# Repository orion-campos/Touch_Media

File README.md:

# INFO
- Thesis Project Title: Touch Media
- MASTER IN ADVANCED ARCHITECTURE
- Institute of Advanced Architecture of Catalonia IAAC
- Research Line: Advanced Interaction 2015
- Author: Orion Gorrão Moreira Campos
- GitHub: [https://github.com/orion-campos/Touch_Media](https://github.com/orion-campos/Touch_Media)
- Thesis book: [https://issuu.com/home/published/orion_booklet](https://issuu.com/home/published/orion_booklet)
- Video 1: [Touch Media - Electronic Development](https://vimeo.com/manage/videos/140458246)
- Video 2: [Touch Media - 3D Printing Development](https://vimeo.com/manage/videos/140481266)

# GENERAL INFORMATION
This project is the result of six months of theoretical research and three months of complete dedication at the research line Advanced Interaction, as part of the Master of Advanced Architecture program at the Institute of Advanced Architecture of Catalonia. Because of this, it is possible to develop it more with proper time and resources.<br>
The author is sharing it under under the Apache License Version 2.0, so like other free software licenses, it allows the user of the software the freedom to use for any purpose, to distribute it, to modify it, and to distribute modified versions of the software. It still requires application of the same license to all unmodified parts and, in every licensed file, any original copyright, patent, trademark, and attribution notices in redistributed code must be preserved and, in every licensed file changed, a notification must be added stating that changes have been made to that file. The README file should be ALWAYS MAINTAINED IN ALL COPIES.<br>
Feel free to contact me if necessary :blush:<br>
<br>

# GITHUB FILES
**3D:**<br>
All the 3D printed geometries for the electronic compartments of the first user (the wrist) and the second user (the back pack and the DC motors vibrators). There is the original Rhino file of all, if it is desired to modify anything, and the STL of each part for being 3D printed.<br>
**ARDUINO:**<br>
All the Arduino codes, photos of the circuits, and the Fritzing files of each of the main steps of the development of the project, including the final one. They are organized numerically from 1 to FINAL.<br>
**CONCEPT:**<br>
Illustrations showing the initial concept of the objects that were aimed to create. The illustrations are conceptual, so they form just represent a desirable initial feeling.<br>
**EAGLE_PCBmilling:**<br>
Eagle files of the PCB’s made for the Arduino shields of the Arduino Micro (First user - emitter) and the Arduino UNO (Second user - receiver). Together with all the Eagle files, also the bitmap masks of each board, with the engrave and cut information for the Fabmodules to run.<br>
**PHOTOS:**<br>
Photos of the final prototype of the Glove part and the Back-pack part.<br>
**NOTICE:**<br>
The current Markdown file, that must be included as a readable copy within a README file distributed as part of the derivative works, within the source form or documentation, or within a display generated by the derivative works, as stipulated under the Apache License Version 2.0.<br>

# OBJECTIVE
This research aims to create a new way of communication using and increasing our sense of touch by creating a wearable tool, which has an open use, but in this research will focus to give a critical answer to our major visual based society. The main areas where this new form of communication can be used are:
- Helping vision disabled people, which then could have another option to communicate other than the braille language;
- Connecting users in a long distant relationship, which want to experience another type of connection that the visual devices cannot create; and
- People who want to experience and receive other types of information that couldn‘t been send by visual communication devices.

# PRODUCED OBJECT
A glove wearied by the first user, with 3 flex-sensors and 2 pressure sensors. This glove would be connected to a box attached to the wrist of the first user, containing all the electronic parts necessary to code the information from those sensors and send, via a radio frequency emitter, the information to the second user.<br>
The second user would be wearing a little back-pack with all the electronic parts necessary to code the information received via a radio frequency receiver, and transform it into movement of 6 DC Motors attached to its back, that would turn and rotate a weight on each motor, making the whole enclosure vibrate. The intensity and the length of the vibration of each motor would be determined by the intensity and the length of each sensor being pressed or bended.

# ELECTRONIC AND CODING TOOLS AND METHODS USED
The whole prototype of the electronic and coding part of the project was done with the open-source computer hardware and software Arduino.<br>
Arduino is based on a family of micro-controller board manufactured primarily by SmartProjects in Italy, using various 8-bit Atmel AVR micro-controllers or 32-bit Atmel ARM processors. These systems provide sets of digital and analog I/O pins that can be interfaced to various expansion boards and other circuits. The boards feature serial communications interfaces, including USB on some models, for loading programs from personal computers. For programming the micro-controllers, the Arduino platform provides an integrated development environment (IDE) based on the Processing project, which includes support for C and C++ programming languages.<br>
After the electronic prototype part it was used the software Fritzing, which is an open source software initiative to support designers and artists. It was developed at the University of Applied Sciences of Potsdam. The main advantage of the software is the easy interface to document and record the layout of the created breadboards.<br>

# ELECTRONIC COMPONENTS LIST
### First user - emitter
GLOVE PART
- 1x Arduino Micro;
- 1x RF Link Transmitter - 315MHz (https://www.sparkfun.com/products/10535);
- 3x Long Flex sensor-Length: 112.5mm (https://www.adafruit.com/products/182);
- 2x Round Force-Sensitive Resistor (FSR) - Interlink 402-Length:: 56.77mm (https://www.adafruit.com/products/166);
- 6x 22Kohm Resistor;
- 1x 10Kohm Resistor;
- 1x 220ohm Resistor;
- 1x LED;
- 1x Simple Switch;
- 1x 7.4V 400mAh Lipo battery; and
- 30CMx Hard copper wire to serve as antenna.

### Second user - receiver
BACK PACK PART
- 1x Arduino UNO R2 (UNO R3 should work as well);
- 1x RF Link Receiver - 4800bps (315MHz) (https://www.sparkfun.com/products/10533);
- 6x 1N4004 Diode;
- 6x TIP120 Transistor;
- 6x 10Kohm Resistor;
- 1x Simple Switch;
- 1x 7.4V 400mAh Lipo battery;
- 4x AA battery;
- 2x Double AA battery holder;
- 1x 7.4V 400mAh Lipo battery; and
- 30centimeterx Hard copper wire to serve as antenna.

VIBRATORS PART
- 6x 1.5-4.5V DC Motor (130 size).

### NECESSARY ELECTRONIC SUPPLIES
- 1x Lipo battery charger;
- 1x USB cable - A/MicroB;
- 1x USB Cable - Standard A-B;
- 1x Cooper plate for PCB milling;
- 5meterx Soft core electronic wire (aprox.28AWG); and
- 1x Soldering iron.

### OPTIONAL ELECTRONIC SUPPLIES
- 2meterx 6mm Heat Shrink.

# CIRCUIT BOARD PROJECT AND METHOD OF FABRICATION
After all the electronic components were tested and improved at the Protoboard, it was necessary to make a final shield for the Arduino in order to decrease the size of the circuit, make it user friendly, and more important, make it portable!<br>
It was used the software CAD Soft EAGLE for creating the schematic and the board design. EAGLE (for: Easily Applicable Graphical Layout Editor, German: Einfach anzuwendender grafischer Layout-Editor) by CadSoft Computer is a flexible, expandable and scriptable EDA application with schematic capture editor, PCB layout editor, auto-router and CAM and BOM tools developed by CadSoft Computer GmbH, Germany, since 1988. EAGLE is popular among smaller design houses and in academia for its favorable licensing terms and rich availability of component libraries on the web. Hobbyists are attracted by the availability of freeware licenses.<br>
After the board was designed with the most efficient use of the small space available, the CNC code was generated. Due to try and error process, a more fast speed configuration was used, making only five offset paths of cut in each line. The software used for this was the Fabmodules.<br>
- Video 1: [Touch Media - Electronic Development](https://vimeo.com/manage/videos/140458246)

# HARDWARE METHOD OF FABRICATION
For fabricating the cases of the DC Motors, the Arduino‘s and the produced Shields, it was created a series of compartments using a 3D Printer. This option was chosen due to the geometry that would be created, and the possibility to change and improve the final result easily.<br>
The method of 3D Printing used was an additive one, using PLA filaments. The 3d Printer was the BCN3D+, an open hardware based on the mechanic of the RapRap Prussa, developed by the Universidad Politecnica de Catalunya and assembled by the author.<br>
The file for the machine to print is know as G-Code. This file is a series of numbers that represent the position of the Nozller and the speed that the extruder need to go to the current point from the previous point. The G-Code was generated using the Slic3r software, a free software that generate the G-Code file, by configurations defined by the user, such as height of each layer, temperature, percentage of the fill of each solid, style of the fill, etc. The Slic3r software need as a basic input the base geometry to be 3d printed. This geometry was made using the Rhino software, but could be generated by any major 3D modeler.<br>
- Video 2: [Touch Media - 3D Printing Development](https://vimeo.com/manage/videos/140481266)

# FINAL CONCLUSION
The project opened a broad range of possibilities for improvement.<br>
The choose for a radio frequency board to send the data from one Arduino to the other had some advantages, a couple of backfires on the project happened. One of them was the delay of information that was intentionally set from the time that the data is received from the Arduino to the moment that it is translated to movement to the DC Motors vibrators. This delay needed to be long enough as one second to not over-load the radio frequency receiver. Although one second don‘t appear to be a long period, it jeopardize the sense of instant response of the device.<br>
Another weak point of the choosen radio frequency components was that radio frequency devices are extremely suitable by noise pollution caused by electrostatic that are each day increasing in our society. The scenario get worst since the project is using so many electric motors, which generate a extremely big electromagnetic field. The coil produced by the motors interfere a lot on the radio frequency receiver, being very frequent on this project to receive a “dirty data“. The sender part is not affected.<br>
The main advantages for using the radio frequency boards was the simpler code that they demand in comparison with a internet connection option. Also this option was choose to create an accessible project to be reproduced later in the maker community, since it has been choose a low cost radio frequency transmitters and receivers (each ranging fro 8€ to 12€).<br>
There are more stable already made shields, but their price range between 40€ to 50€, which would become hard to be freely reproduced.<br>
The ideal way of communication would be made the connection through internet, which would achieve the desired effect of creating a functional new way of communication other than the cellphones and other common visual devices that are available today.<br>
Other than this, one of the main points to emphasize is that although this project aims to create a new way of communication, it would never be the same as the existing way of communications, which are based on the written language and speak language, because those forms of languages are based on different senses, as the vision and hearing sense. This project demands to develop a language in order to communicate through the touch sense. There would not be a substitute for a twitter send from a cellphone, or written message telling specific information. Other than this, the information sent could be of a specific feeling such as love, hate, or gratitude.<br>
The point that could be develop from this project, but demand years of research are the areas that should be excited on the body in order to create this set of desired emotions. This would demand a better research on the physical part of the motors and also a biological, medical and psychological team.<br>
- Thesis book: [https://issuu.com/home/published/orion_booklet](https://issuu.com/home/published/orion_booklet)

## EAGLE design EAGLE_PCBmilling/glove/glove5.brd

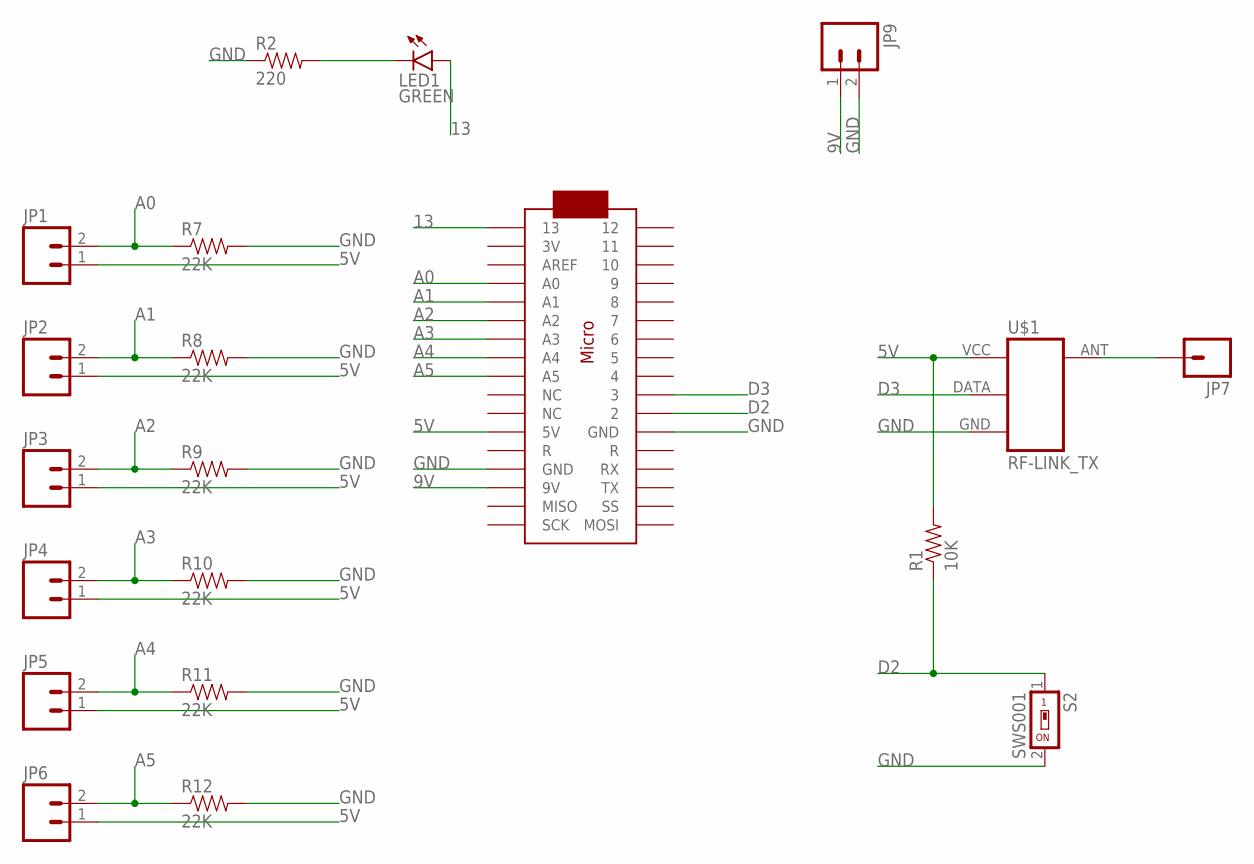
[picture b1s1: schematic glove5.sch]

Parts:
JP1, JP2, JP3, JP4, JP5, JP6, JP9: M02LOCK_LONGPADS; 1X02_LOCK_LONGPADS
JP7: M01PTH_LONGPAD; 1X01_LONGPAD
LED1: GREEN; FKIT-LED-1206
R1: 10K; 1206
R2: 220; 1206
R7, R8, R9, R10, R11, R12: 22K; 1206
S2: SWS001; SMS-001
U$1: RF-LINK_TX
U$3: ARDUINOMICRO

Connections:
5V: JP1.1, JP2.1, JP3.1, JP4.1, JP5.1, JP6.1, R1.2, U$1.VCC (+5V), U$3.P$23 (5V)
9V: JP9.1, U$3.P$20 (9V)
13: LED1.A, U$3.P$34 (13)
A0: JP1.2, R7.1, U$3.P$31 (A0)
A1: JP2.2, R8.1, U$3.P$30 (A1)
A2: JP3.2, R9.1, U$3.P$29 (A2)
A3: JP4.2, R10.1, U$3.P$28 (A3)
A4: JP5.2, R11.1, U$3.P$27 (A4)
A5: JP6.2, R12.1, U$3.P$26 (A5)
D2: R1.1, S2.1, U$3.P$11 (2)
D3: U$1.DATA, U$3.P$10 (3)
GND: JP9.2, R2.1, R7.2, R8.2, R9.2, R10.2, R11.2, R12.2, S2.2, U$1.GND, U$3.P$12 (GND), U$3.P$21 (GND)
unnamed: JP7.1, U$1.ANT
unnamed: LED1.C, R2.2

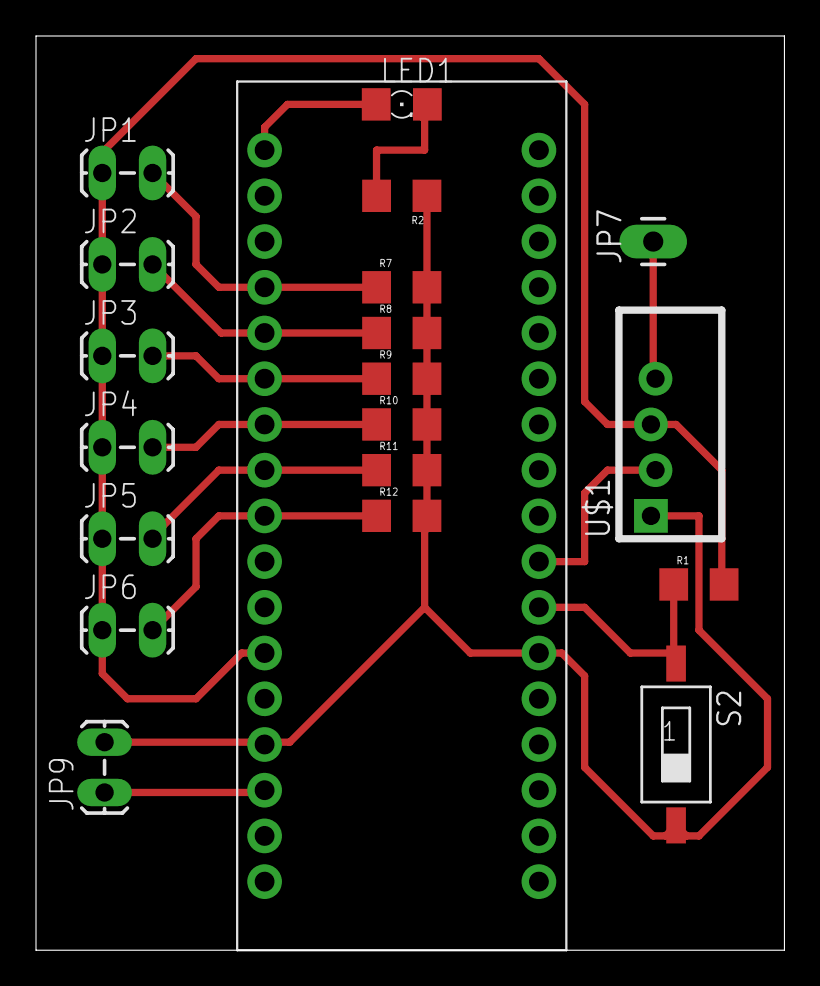
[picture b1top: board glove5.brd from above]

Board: 2 copper layers, 41.6 x 50.8 mm, 20 parts (0 on the bottom side), 14 nets.

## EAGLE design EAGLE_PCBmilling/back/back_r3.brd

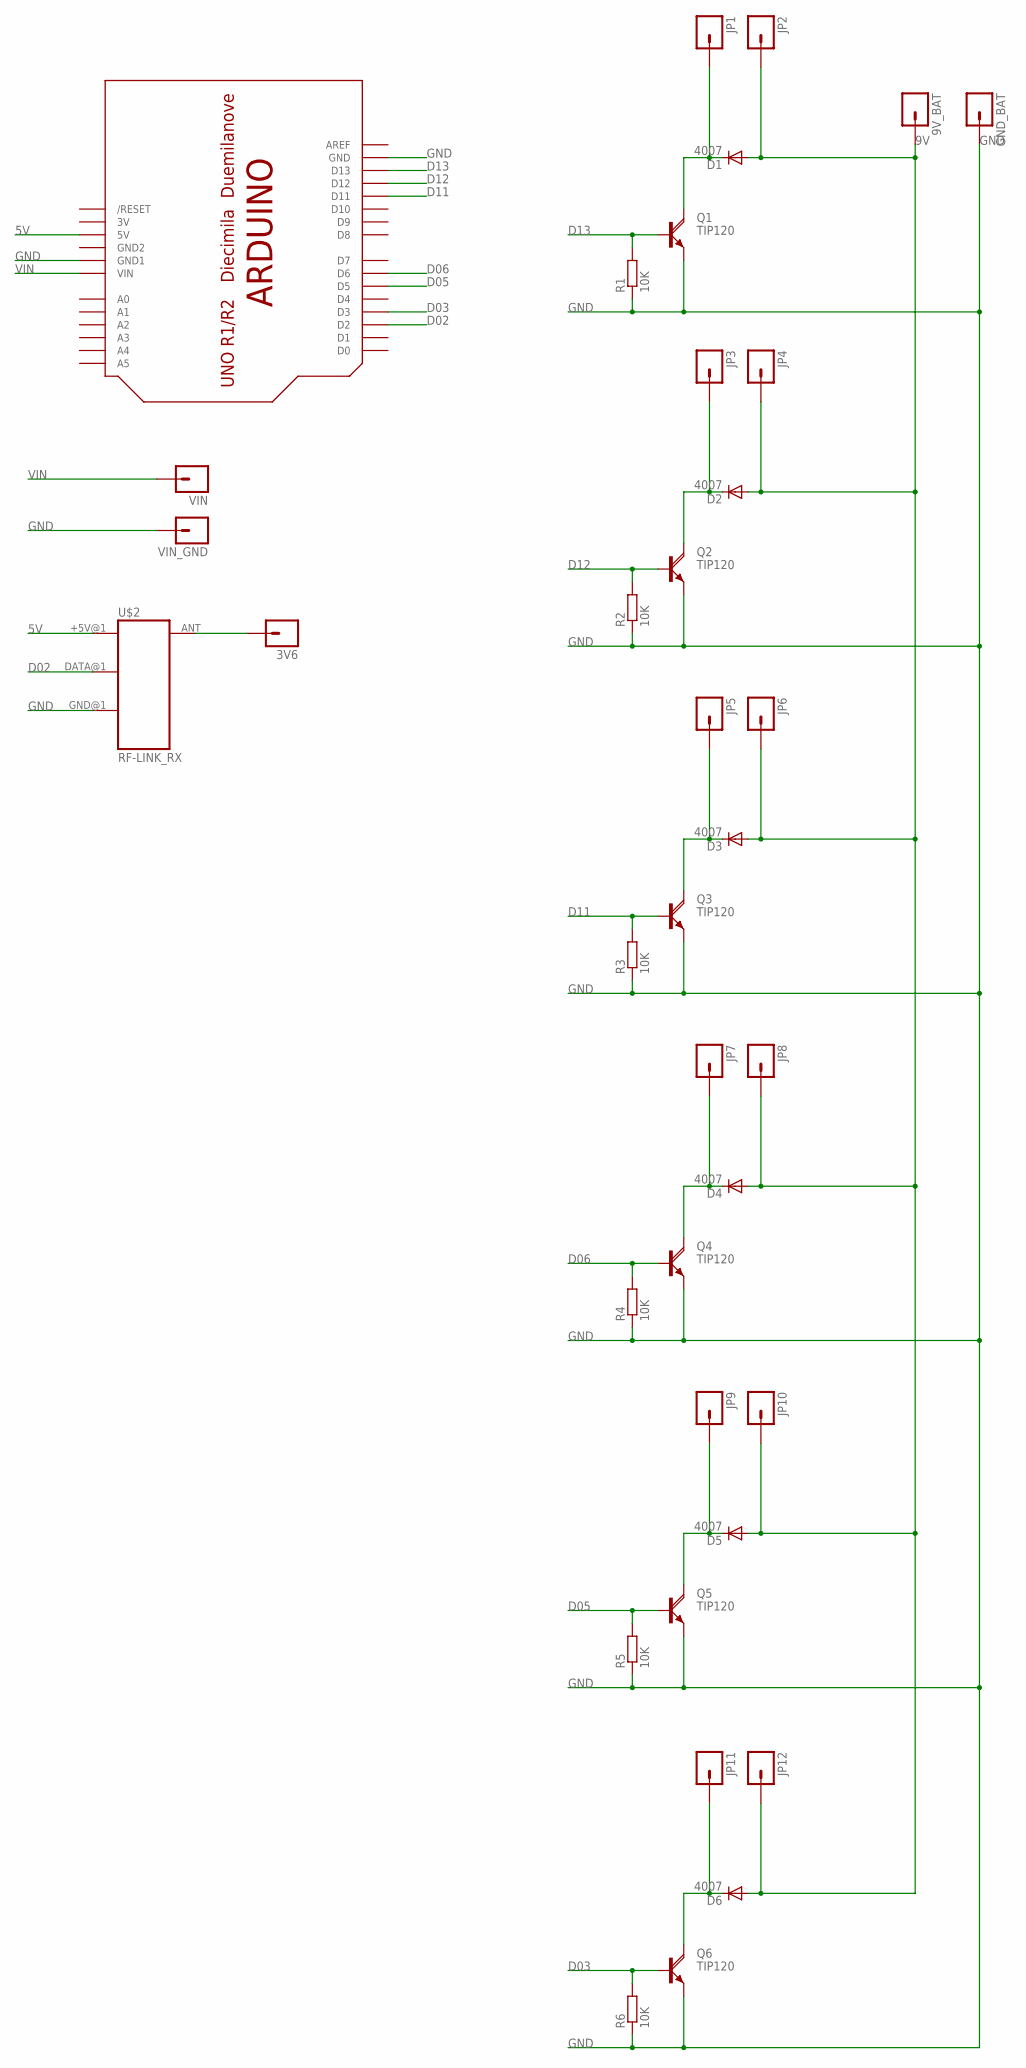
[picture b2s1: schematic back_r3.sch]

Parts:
3V6, 9V_BAT: M01PTH_LONGPAD; 1X01_LONGPAD
D1, D2, D3, D4, D5, D6: 4007; DO41-10
GND_BAT: M01PTH_LONGPAD; 1X01_LONGPAD
JP1, JP2, JP3, JP4, JP5, JP6, JP7, JP8, JP9, JP10, JP11, JP12: M01PTH_LONGPAD; 1X01_LONGPAD
Q1, Q2, Q3, Q4, Q5, Q6: TIP120; TO220AH
R1, R2, R3, R4, R5, R6: 10K; 0207/10
U$1: ARDUINO-BPLACE
U$2: RF-LINK_RX
VIN: M01PTH_LONGPAD; 1X01_LONGPAD
VIN_GND: M01PTH_LONGPAD; 1X01_LONGPAD

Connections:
3V: U$1.3V
5V: U$1.5V, U$2.+5V@1 (+5V)
9V: 9V_BAT.1, D1.A, D2.A, D3.A, D4.A, D5.A, D6.A, JP2.1, JP4.1, JP6.1, JP8.1, JP10.1, JP12.1
D02: U$1.D2, U$2.DATA@1 (DATA)
D03: Q6.B, R6.2, U$1.D3
D05: Q5.B, R5.2, U$1.D5
D06: Q4.B, R4.2, U$1.D6
D11: Q3.B, R3.2, U$1.D11
D12: Q2.B, R2.2, U$1.D12
D13: Q1.B, R1.2, U$1.D13
GND: GND_BAT.1, Q1.E, Q2.E, Q3.E, Q4.E, Q5.E, Q6.E, R1.1, R2.1, R3.1, R4.1, R5.1, R6.1, U$1.GND, U$1.GND1, U$2.GND@1 (GND), VIN_GND.1
GND2: U$1.GND2
unnamed: 3V6.1, U$2.ANT
unnamed: D1.C, JP1.1, Q1.C
unnamed: D2.C, JP3.1, Q2.C
unnamed: D3.C, JP5.1, Q3.C
unnamed: D4.C, JP7.1, Q4.C
unnamed: D5.C, JP9.1, Q5.C
unnamed: D6.C, JP11.1, Q6.C
VIN: U$1.VIN, VIN.1

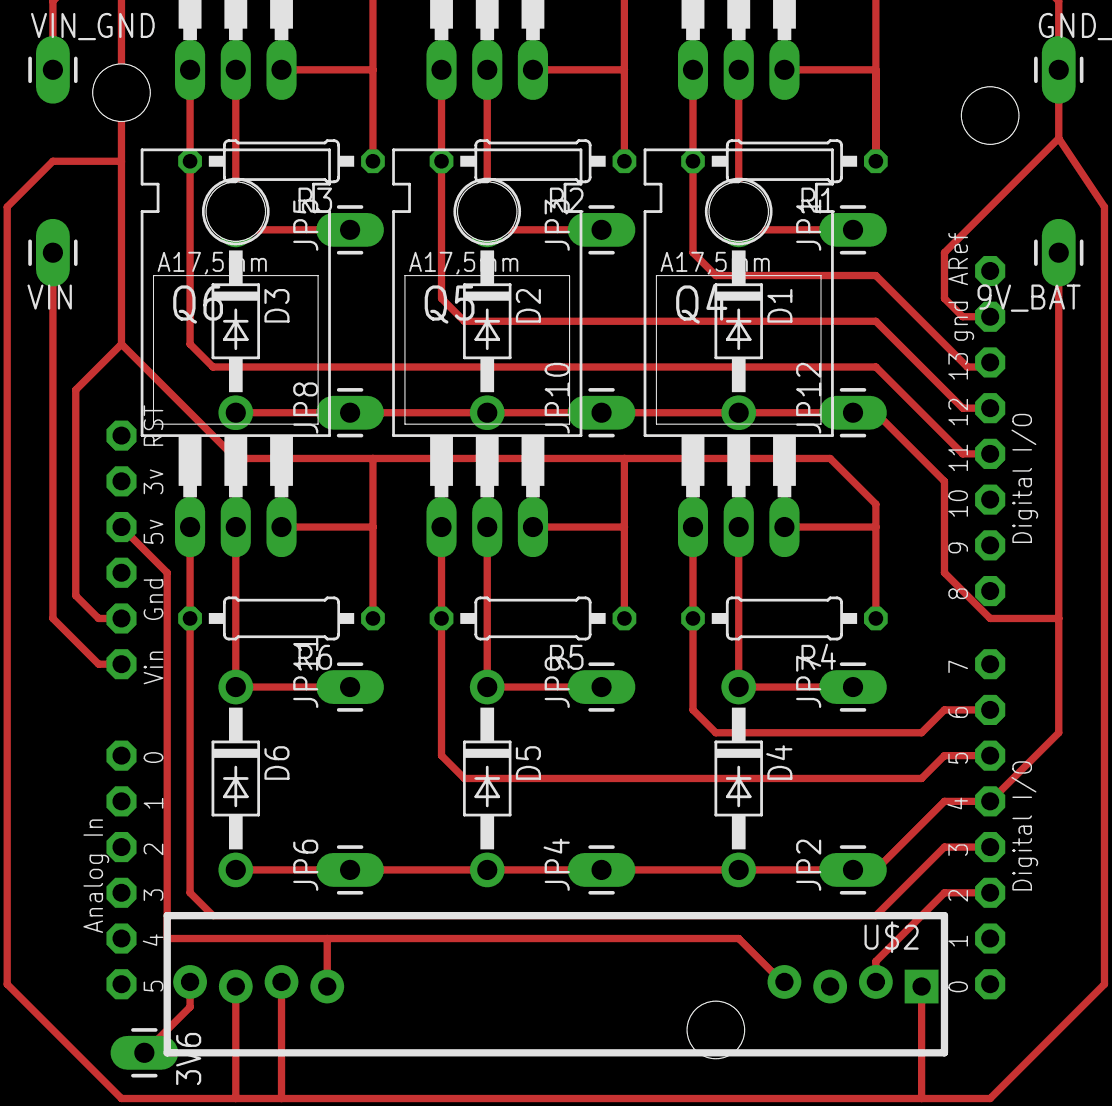
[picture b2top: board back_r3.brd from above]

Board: 2 copper layers, 37 parts (0 on the bottom side), 18 nets.

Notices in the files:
README.md:
https://img.shields.io/badge/Creative%20Commons-EF9421?style=for-the-badge&logo=creativecommons&logoColor=white
parts and their libraries:
SparkFun-Connectors: Licensing: Creative Commons ShareAlike 4.0 International - https://creativecommons.org/licenses/by-sa/4.0
